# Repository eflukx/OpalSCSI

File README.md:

# OpalSCSI

Nice, tidy and small BlueSCSI-compatible dongle made to fit classic Macintosh computers. (But probably fits a whole lot more machines sporting a DB-25 SCSI connector!)

## Background

I found an old Macintosh 512k lying around and obviously ~~wanted~~ needed to boot it. It did come with a (rather large) box containing a SCSI drive, but unfortunately/unsurprisingly it did not stand the test of time.. 🥹
So with no apparent way to be able to boot my Mac and no appetite to fiddle with old SCSI drives I stumbled upon the great BlueSCSI project! I loved the project and decided build some hardware to go with the firmware. The design for this is what you find in this repository.
I had all components needed and I did not want to fiddle with loose (dupont) wiring to a bluepill or SCSI cabling or whatever. Therefore decided to build a small dongle board that takes a SD-card and directly plugs into the computer.

## Some nice pictas

<!--  -->
<!--  -->

## Get one of my boards!

I've had some (5) boards produced and soldered 2 devices together for own use. As I still have some boards lying around, you can get one at shipping cost! 🥳 Just create an issue here with the request, I'll probably pick it up.. :)

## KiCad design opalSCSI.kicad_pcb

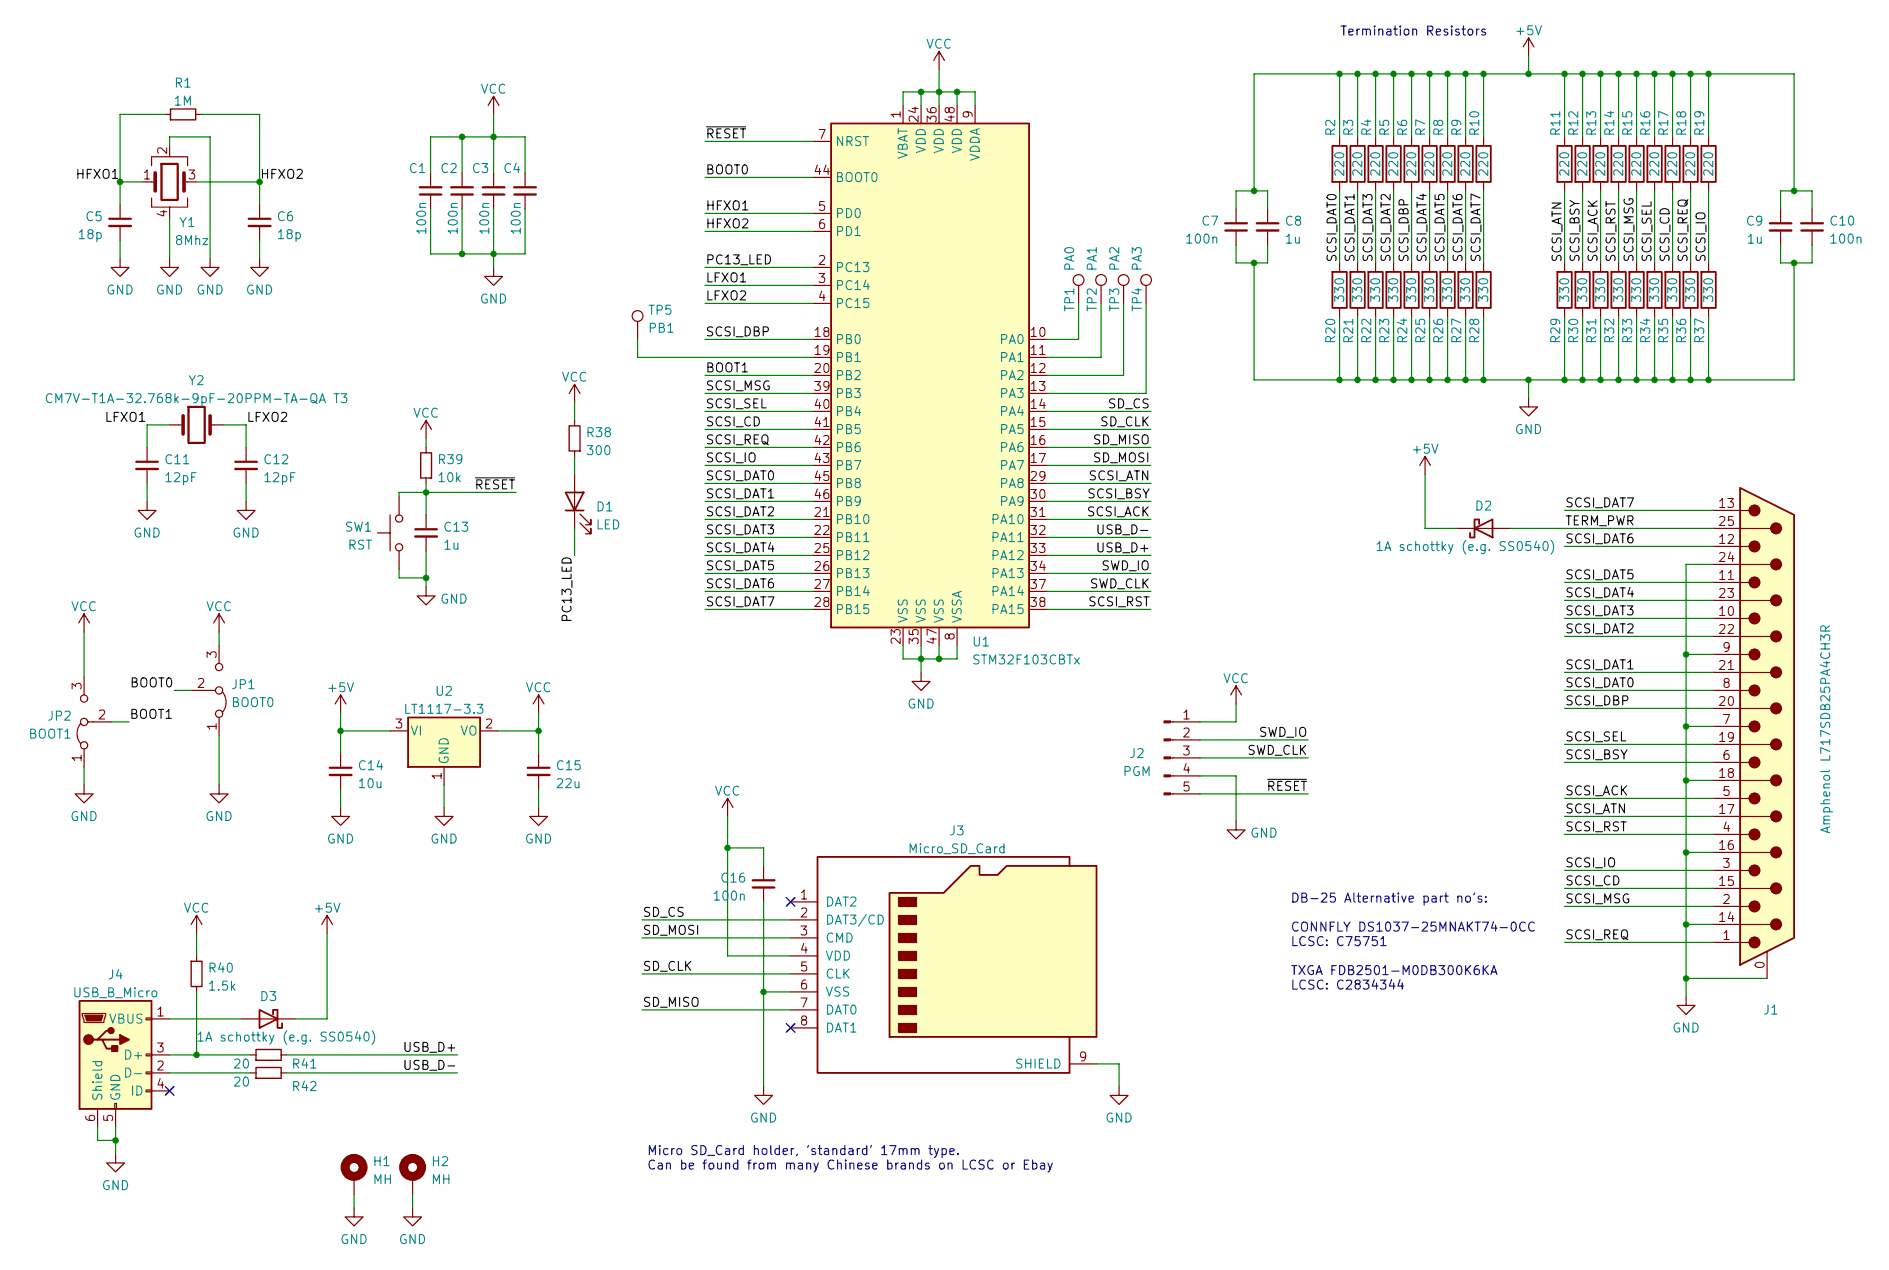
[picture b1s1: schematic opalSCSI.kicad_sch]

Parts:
C1, C2, C3, C4, C7, C10, C16: 100n; C_0603_1608Metric
C5, C6: 18p; C_0603_1608Metric
C8, C9, C13: 1u; C_0603_1608Metric
C11, C12: 12pF; C_0603_1608Metric
C14: 10u; C_0603_1608Metric
C15: 22u; C_0805_2012Metric
D1: LED; LED_0603_1608Metric_Pad1.05x0.95mm_HandSolder
D2, D3: 1A schottky (e.g. SS0540); D_SOD-123
H1, H2: MH; MountingHole_2.7mm_M2.5_ISO14580_Pad
J1: Amphenol L717SDB25PA4CH3R; DSUB-25_Male_Horizontal_P2.77x2.84mm_EdgePinOffset7.70mm_Ho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
J2: PGM; PinHeader_1x05_P2.54mm_Vertical
J3: Micro_SD_Card; Micro_SD_socket_Ebay
J4: USB_B_Micro; USB_Micro-B_2_Holes
JP1: BOOT0; SolderJumper-3_P1.3mm_Bridged12_Pad1.0x1.5mm
JP2: BOOT1; SolderJumper-3_P1.3mm_Bridged12_Pad1.0x1.5mm
R1: 1M; R_0603_1608Metric
R2, R3, R4, R5, R6, R7, R8, R9, R10, R11, R12, R13, R14, R15, R16, R17, R18, R19: 220; R_0603_1608Metric
R20, R21, R22, R23, R24, R25, R26, R27, R28, R29, R30, R31, R32, R33, R34, R35, R36, R37: 330; R_0603_1608Metric
R38: 300; R_0603_1608Metric
R39: 10k; R_0603_1608Metric
R40: 1.5k; R_0603_1608Metric
R41, R42: 20; R_0603_1608Metric
SW1: RST; SW_SPST_TL3305B
TP1: PA0; TestPoint_Pad_D1.5mm
TP2: PA1; TestPoint_Pad_D1.5mm
TP3: PA2; TestPoint_Pad_D1.5mm
TP4: PA3; TestPoint_Pad_D1.5mm
TP5: PB1; TestPoint_Pad_D1.5mm
U1: STM32F103CBTx; LQFP-48_7x7mm_P0.5mm
U2: LT1117-3.3; SOT-223-3_TabPin2
Y1: 8Mhz; Crystal_SMD_3225-4Pin_3.2x2.5mm
Y2: CM7V-T1A-32.768k-9pF-20PPM-TA-QA T3; Crystal_SMD_MicroCrystal_CC7V-T1A-2Pin_3.2x1.5mm

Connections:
+5V: C7.2, C8.1, C9.1, C10.2, C14.1, D2.1 (K), D3.1 (K), R2.1, R3.1, R4.1, R5.1, R6.1, R7.1, R8.1, R9.1, R10.1, R11.1, R12.1, R13.1, R14.1, R15.1, R16.1, R17.1, R18.1, R19.1, U2.3 (VI)
/BOOT0: JP1.2 (C), U1.44 (BOOT0)
/BOOT1: JP2.2 (C), U1.20 (PB2)
/HFXO1: C5.1, R1.1, U1.5 (PD0), Y1.1
/HFXO2: C6.1, R1.2, U1.6 (PD1), Y1.3
/LFXO1: C11.1, U1.3 (PC14), Y2.1
/LFXO2: C12.1, U1.4 (PC15), Y2.2
/PC13_LED: D1.1 (K), U1.2 (PC13)
/SCSI_ACK: J1.5, R13.2, R31.2, U1.31 (PA10)
/SCSI_ATN: J1.17, R11.2, R29.2, U1.29 (PA8)
/SCSI_BSY: J1.6, R12.2, R30.2, U1.30 (PA9)
/SCSI_CD: J1.15, R17.2, R35.2, U1.41 (PB5)
/SCSI_DAT0: J1.8, R2.2, R20.2, U1.45 (PB8)
/SCSI_DAT1: J1.21, R3.2, R21.2, U1.46 (PB9)
/SCSI_DAT2: J1.22, R5.2, R23.2, U1.21 (PB10)
/SCSI_DAT3: J1.10, R4.2, R22.2, U1.22 (PB11)
/SCSI_DAT4: J1.23, R7.2, R25.2, U1.25 (PB12)
/SCSI_DAT5: J1.11, R8.2, R26.2, U1.26 (PB13)
/SCSI_DAT6: J1.12, R9.2, R27.2, U1.27 (PB14)
/SCSI_DAT7: J1.13, R10.2, R28.2, U1.28 (PB15)
/SCSI_DBP: J1.20, R6.2, R24.2, U1.18 (PB0)
/SCSI_IO: J1.3, R19.2, R37.2, U1.43 (PB7)
/SCSI_MSG: J1.2, R15.2, R33.2, U1.39 (PB3)
/SCSI_REQ: J1.1, R18.2, R36.2, U1.42 (PB6)
/SCSI_RST: J1.4, R14.2, R32.2, U1.38 (PA15)
/SCSI_SEL: J1.19, R16.2, R34.2, U1.40 (PB4)
/SD_CLK: J3.5 (CLK), U1.15 (PA5)
/SD_CS: J3.2 (DAT3/CD), U1.14 (PA4)
/SD_MISO: J3.7 (DAT0), U1.16 (PA6)
/SD_MOSI: J3.3 (CMD), U1.17 (PA7)
/SWD_CLK: J2.3, U1.37 (PA14)
/SWD_IO: J2.2, U1.34 (PA13)
/TERM_PWR: D2.2 (A), J1.25
/USB_D+: R41.2, U1.33 (PA12)
/USB_D-: R42.2, U1.32 (PA11)
/~RESET: C13.1, J2.5, R39.1, SW1.2, U1.7 (NRST)
GND: C1.1, C2.1, C3.1, C4.1, C5.2, C6.2, C7.1, C8.2, C9.2, C10.1, C11.2, C12.2, C13.2, C14.2, C15.2, C16.1, H1.1, H2.1, J1.0 (PAD), J1.7, J1.9, J1.14, J1.16, J1.18, J1.24, J2.4, J3.6 (VSS), J3.9 (SHIELD), J4.5 (GND), J4.6 (Shield), JP1.1 (A), JP2.1 (A), R20.1, R21.1, R22.1, R23.1, R24.1, R25.1, R26.1, R27.1, R28.1, R29.1, R30.1, R31.1, R32.1, R33.1, R34.1, R35.1, R36.1, R37.1, SW1.1, U1.8 (VSSA), U1.23 (VSS), U1.35 (VSS), U1.47 (VSS), U2.1 (GND), Y1.2, Y1.4
unnamed: D1.2 (A), R38.1
unnamed: D3.2 (A), J4.1 (VBUS)
unnamed: J4.2 (D-), R42.1
unnamed: J4.3 (D+), R40.2, R41.1
unnamed: TP1.1, U1.10 (PA0)
unnamed: TP2.1, U1.11 (PA1)
unnamed: TP3.1, U1.12 (PA2)
unnamed: TP4.1, U1.13 (PA3)
unnamed: TP5.1, U1.19 (PB1)
VCC: C1.2, C2.2, C3.2, C4.2, C15.1, C16.2, J2.1, J3.4 (VDD), JP1.3 (B), JP2.3 (B), R38.2, R39.2, R40.1, U1.1 (VBAT), U1.9 (VDDA), U1.24 (VDD), U1.36 (VDD), U1.48 (VDD), U2.2 (VO)

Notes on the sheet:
DB-25 Alternative part no's: CONNFLY DS1037-25MNAKT74-0CC LCSC: C75751 TXGA FDB2501-M0DB300K6KA LCSC: C2834344
Micro SD_Card holder, 'standard' 17mm type. Can be found from many Chinese brands on LCSC or Ebay
Termination Resistors

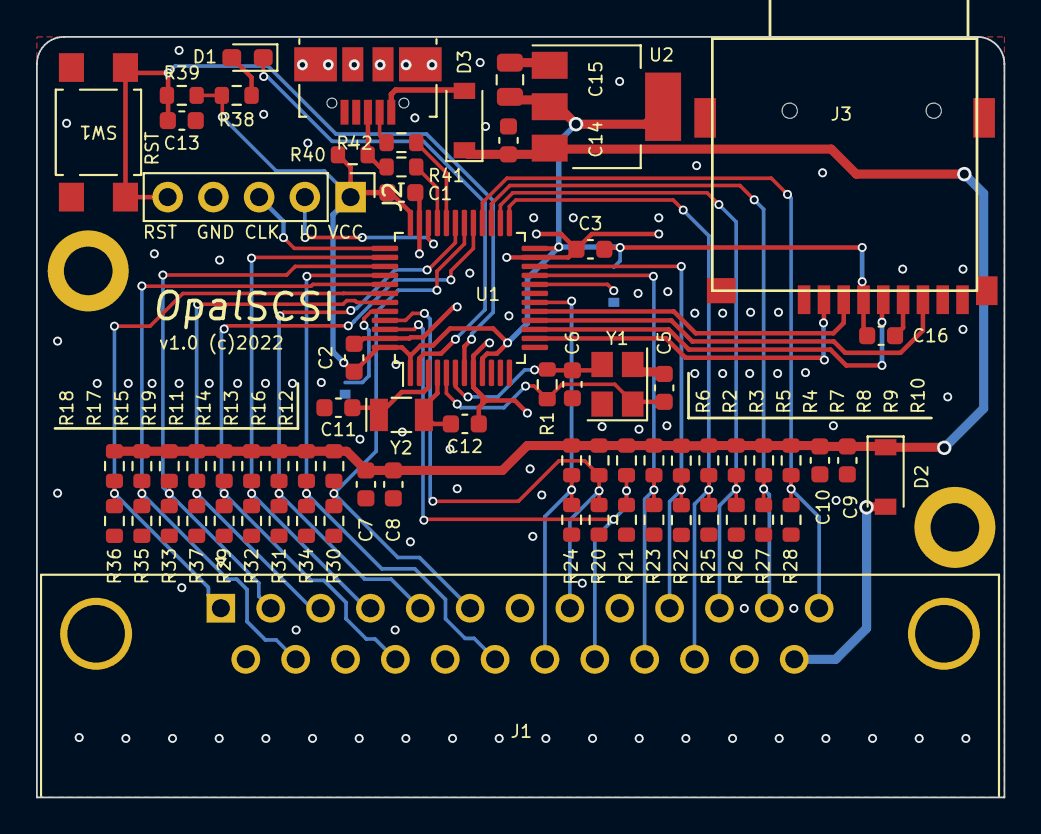
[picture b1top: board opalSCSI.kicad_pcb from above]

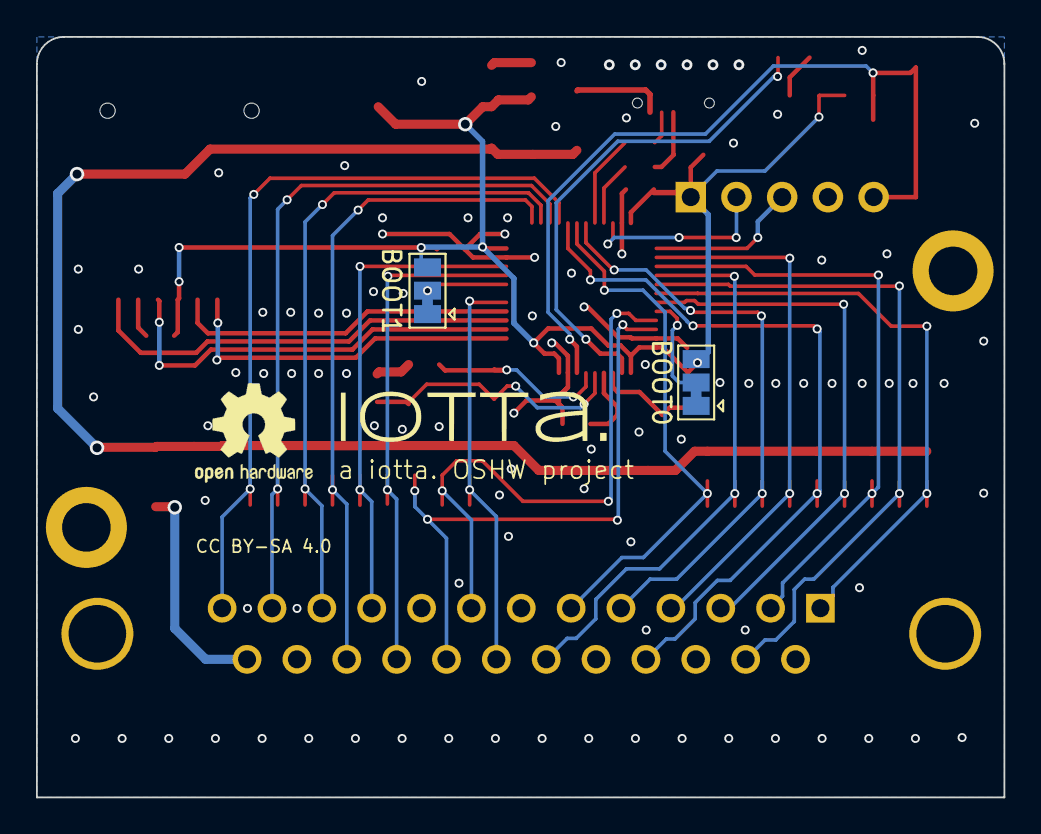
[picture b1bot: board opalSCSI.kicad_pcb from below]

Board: 2 copper layers, 53.8 x 42.2 mm, 73 parts (2 on the bottom side), 42 nets.

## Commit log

2022-07-01 Initial commit, V1.0 mostly done :)
    not built and tested for real yet..
2022-07-07 Add nReset pin to programming (SWD) header
2024-09-04 Why not add a schematics pdf (ony has been 2 years..;)

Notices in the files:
opalSCSI.kicad_pcb:
CC BY-SA 4.0
v1.0 (c)2022
